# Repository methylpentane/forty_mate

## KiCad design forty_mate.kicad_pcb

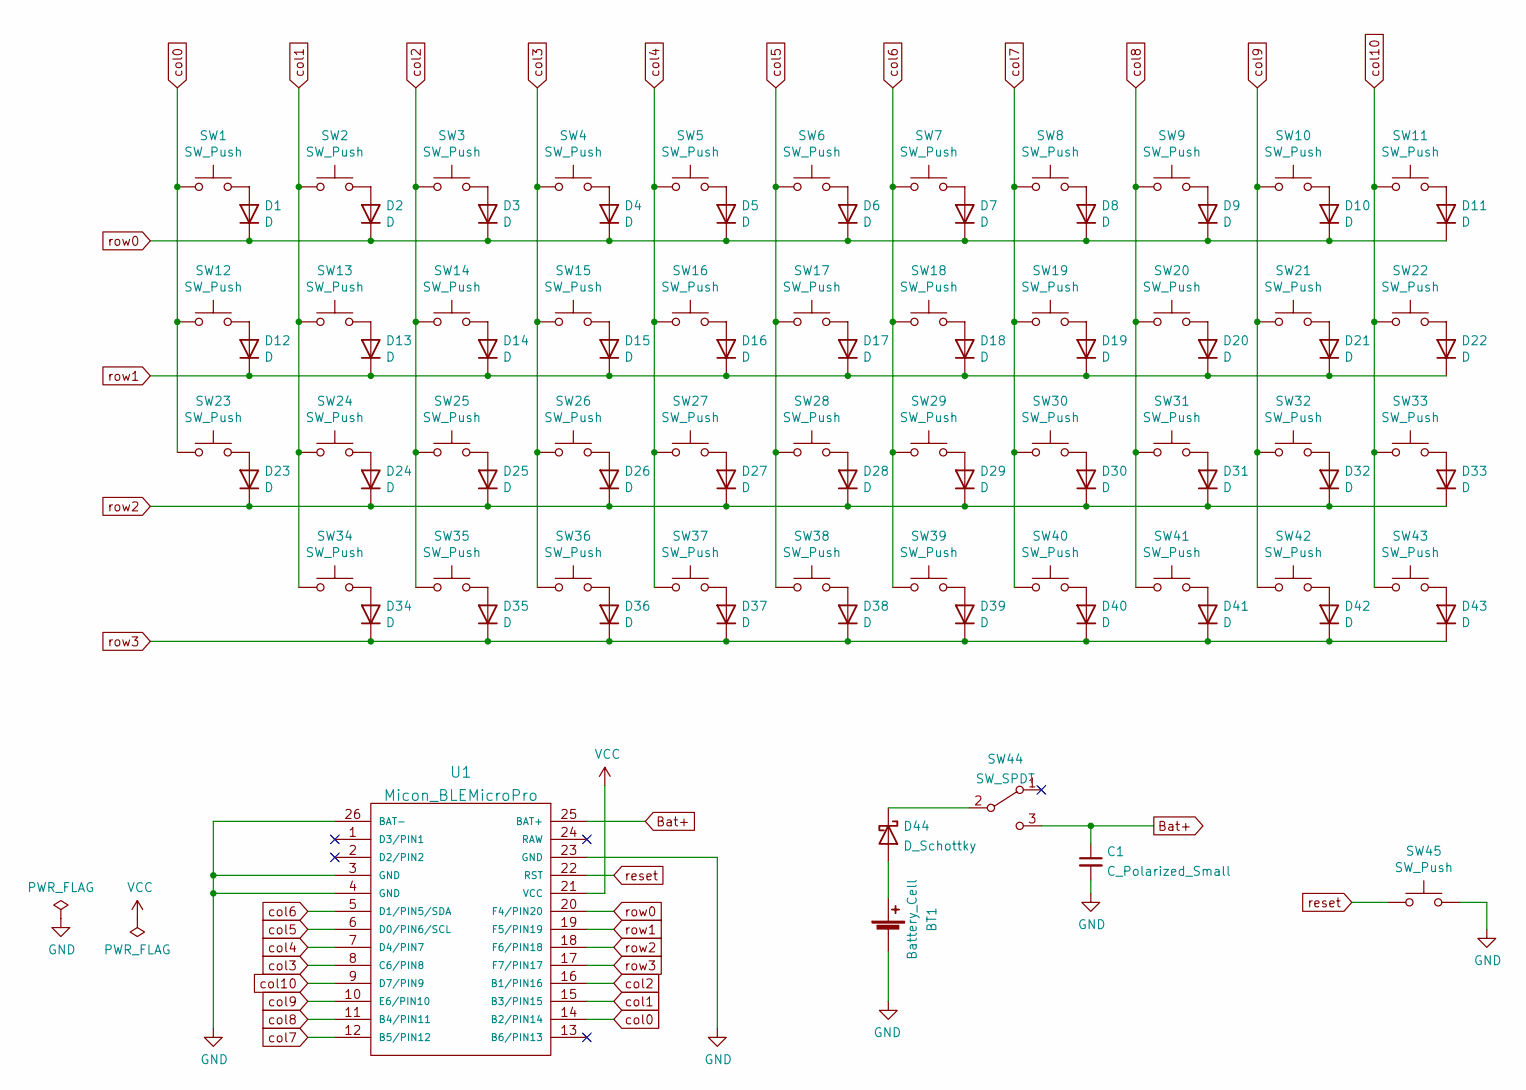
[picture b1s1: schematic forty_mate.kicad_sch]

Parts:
BT1: Battery_Cell; HU1632
C1: C_Polarized_Small; Capacitor_1206
D1, D2, D3, D4, D5, D6, D7, D8, D9, D10, D11, D12, D13, D14, D15, D16, D17, D18, D19, D20, D21, D22, D23, D24, D25, D26, D27, D28, D29, D30, D31, D32, D33, D34, D35, D36, D37, D38, D39, D40, D41, D42, D43: D; Diode_SMD
D44: D_Schottky; Diode_SMD_S-FLAT
SW1, SW2, SW3, SW4, SW5, SW6, SW7, SW8, SW9, SW10, SW11, SW13, SW14, SW15, SW16, SW17, SW18, SW19, SW20, SW21, SW22, SW24, SW25, SW26, SW27, SW28, SW29, SW30, SW31, SW32, SW33, SW34, SW39, SW40, SW41: SW_Push; CherryMX_Hotswap_1u
SW12, SW35, SW38, SW42: SW_Push; CherryMX_Hotswap_1.25u
SW23, SW43: SW_Push; CherryMX_Hotswap_1.75u
SW36: SW_Push; CherryMX_Hotswap_2u_Rev
SW37: SW_Push; CherryMX_Hotswap_2.25u_Rev
SW44: SW_SPDT; TGSW_MK12C02
SW45: SW_Push; ResetSW
U1: Micon_BLEMicroPro; Micon_BMP_7sKB

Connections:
Bat+: C1.1, SW44.3 (C), U1.25 (BAT+)
GND: BT1.2 (-), C1.2, SW45.2, U1.3 (GND), U1.4 (GND), U1.23 (GND), U1.26 (BAT-)
unnamed: BT1.1 (+), D44.2 (A)
unnamed: D1.2 (A), SW1.2
unnamed: D2.2 (A), SW2.2
unnamed: D3.2 (A), SW3.2
unnamed: D4.2 (A), SW4.2
unnamed: D5.2 (A), SW5.2
unnamed: D6.2 (A), SW6.2
unnamed: D7.2 (A), SW7.2
unnamed: D8.2 (A), SW8.2
unnamed: D9.2 (A), SW9.2
unnamed: D10.2 (A), SW10.2
unnamed: D11.2 (A), SW11.2
unnamed: D12.2 (A), SW12.2
unnamed: D13.2 (A), SW13.2
unnamed: D14.2 (A), SW14.2
unnamed: D15.2 (A), SW15.2
unnamed: D16.2 (A), SW16.2
unnamed: D17.2 (A), SW17.2
unnamed: D18.2 (A), SW18.2
unnamed: D19.2 (A), SW19.2
unnamed: D20.2 (A), SW20.2
unnamed: D21.2 (A), SW21.2
unnamed: D22.2 (A), SW22.2
unnamed: D23.2 (A), SW23.2
unnamed: D24.2 (A), SW24.2
unnamed: D25.2 (A), SW25.2
unnamed: D26.2 (A), SW26.2
unnamed: D27.2 (A), SW27.2
unnamed: D28.2 (A), SW28.2
unnamed: D29.2 (A), SW29.2
unnamed: D30.2 (A), SW30.2
unnamed: D31.2 (A), SW31.2
unnamed: D32.2 (A), SW32.2
unnamed: D33.2 (A), SW33.2
unnamed: D34.2 (A), SW34.2
unnamed: D35.2 (A), SW35.2
unnamed: D36.2 (A), SW36.2
unnamed: D37.2 (A), SW37.2
unnamed: D38.2 (A), SW38.2
unnamed: D39.2 (A), SW39.2
unnamed: D40.2 (A), SW40.2
unnamed: D41.2 (A), SW41.2
unnamed: D42.2 (A), SW42.2
unnamed: D43.2 (A), SW43.2
unnamed: D44.1 (K), SW44.2 (B)
VCC: U1.21 (VCC)
col0: SW1.1, SW12.1, SW23.1, U1.14 (B2/PIN14)
col1: SW2.1, SW13.1, SW24.1, SW34.1, U1.15 (B3/PIN15)
col2: SW3.1, SW14.1, SW25.1, SW35.1, U1.16 (B1/PIN16)
col3: SW4.1, SW15.1, SW26.1, SW36.1, U1.8 (C6/PIN8)
col4: SW5.1, SW16.1, SW27.1, SW37.1, U1.7 (D4/PIN7)
col5: SW6.1, SW17.1, SW28.1, SW38.1, U1.6 (D0/PIN6/SCL)
col6: SW7.1, SW18.1, SW29.1, SW39.1, U1.5 (D1/PIN5/SDA)
col7: SW8.1, SW19.1, SW30.1, SW40.1, U1.12 (B5/PIN12)
col8: SW9.1, SW20.1, SW31.1, SW41.1, U1.11 (B4/PIN11)
col9: SW10.1, SW21.1, SW32.1, SW42.1, U1.10 (E6/PIN10)
col10: SW11.1, SW22.1, SW33.1, SW43.1, U1.9 (D7/PIN9)
reset: SW45.1, U1.22 (RST)
row0: D1.1 (K), D2.1 (K), D3.1 (K), D4.1 (K), D5.1 (K), D6.1 (K), D7.1 (K), D8.1 (K), D9.1 (K), D10.1 (K), D11.1 (K), U1.20 (F4/PIN20)
row1: D12.1 (K), D13.1 (K), D14.1 (K), D15.1 (K), D16.1 (K), D17.1 (K), D18.1 (K), D19.1 (K), D20.1 (K), D21.1 (K), D22.1 (K), U1.19 (F5/PIN19)
row2: D23.1 (K), D24.1 (K), D25.1 (K), D26.1 (K), D27.1 (K), D28.1 (K), D29.1 (K), D30.1 (K), D31.1 (K), D32.1 (K), D33.1 (K), U1.18 (F6/PIN18)
row3: D34.1 (K), D35.1 (K), D36.1 (K), D37.1 (K), D38.1 (K), D39.1 (K), D40.1 (K), D41.1 (K), D42.1 (K), D43.1 (K), U1.17 (F7/PIN17)

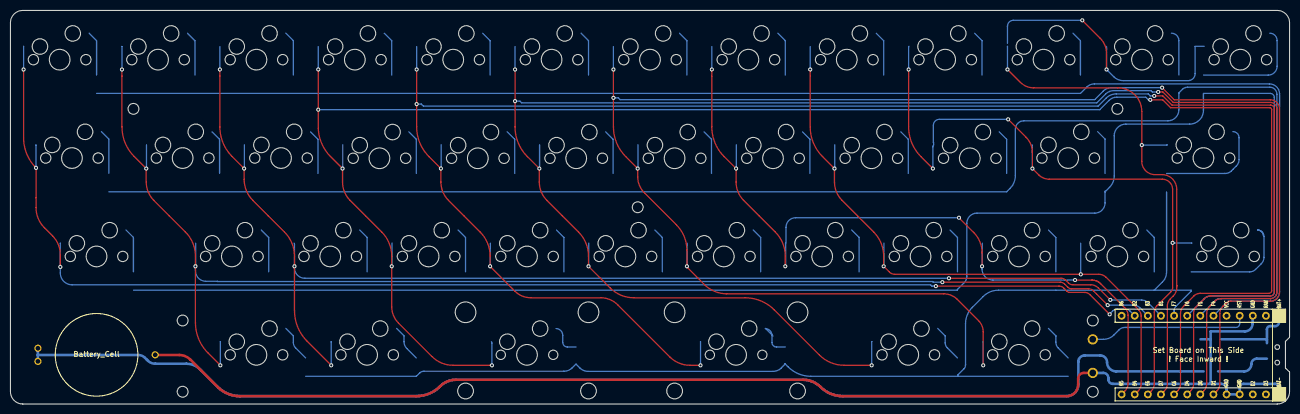
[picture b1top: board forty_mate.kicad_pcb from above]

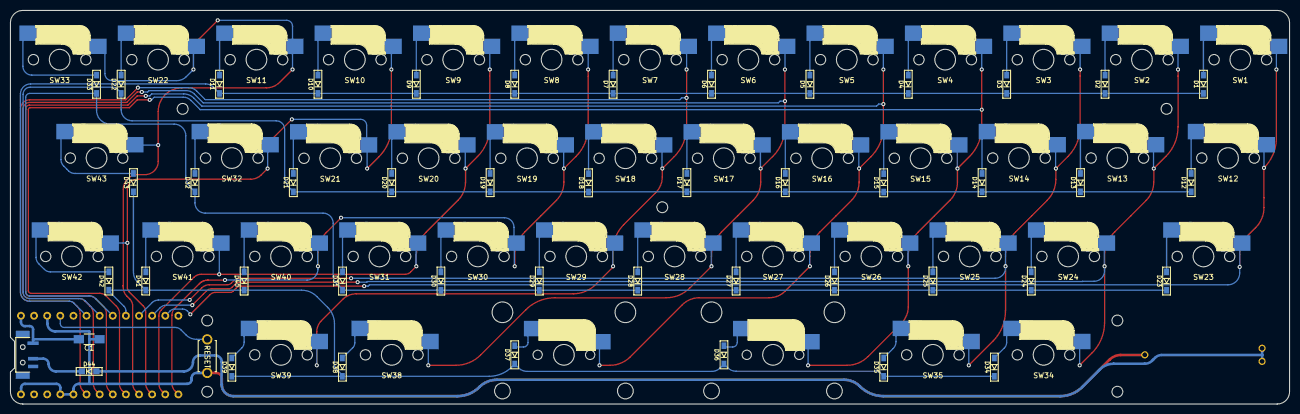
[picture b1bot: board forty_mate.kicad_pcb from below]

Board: 2 copper layers, 247.7 x 76.2 mm, 92 parts (2 on the bottom side), 63 nets.

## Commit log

2022-04-24 first commit 2
2022-05-15 gasket case version
2022-08-21 kari kansei
2022-08-22 karikansei2
2022-09-04 tried some other cell battery footprint
2022-09-04 temporal progress
2022-10-02 second prototype
2022-10-04 tiny mod (ref text of screw hole)
2022-10-04 add switch-plate and more change (true second proto) micon is inside out. changed cell box. switch no tokoro egutte mita
2022-11-22 change screw hole placement
2022-12-01 little change of silk guide
2022-12-01 modify copper pattern
